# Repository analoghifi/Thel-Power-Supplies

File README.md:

# Thel-Power-Supplies
small symmetrical DC power supplies for audio (7W .. 110W | 2x5V .. 2x36V)  

--> https://web.archive.org/web/20180724064052/http://www.thel-audioworld.de/module/NT-HQ/NT-HQ.htm  

see as well the Thel "Black Pulsar" as a special\* kind of very high end power supply -> https://github.com/analoghifi/Thel-Black-Pulsar-PowerSupply  
\*(kinda "Class-A"-Power-Supply --> correctly: constant current parallel shunt voltage regulator)
  
----  
### Kicad projects in this repo:  
* [SPR5-HQ original](https://github.com/analoghifi/Thel-Power-Supplies/tree/main/SPR5-HQ/hardware/KiCad/original) | state: initial release v1.01 | like the original, 1-layer, THT
* [SPR5-HQ "original V2"](https://github.com/analoghifi/Thel-Power-Supplies/tree/main/SPR5-HQ/hardware/KiCad/original%20V2) | state: initial release v1.01 | like the original but improved PCB layout, 1-layer, THT
* [SPR5-HQ improved 2-layer](https://github.com/analoghifi/Thel-Power-Supplies/tree/main/SPR5-HQ/hardware/KiCad/improved%202-layer) | state: coming soon ... | improved, 2-layer PCB, THT

----

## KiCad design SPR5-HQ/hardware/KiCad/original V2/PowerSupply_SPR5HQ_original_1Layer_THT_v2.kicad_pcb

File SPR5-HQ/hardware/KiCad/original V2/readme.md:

this is not the original Thel PCB but it's very like\* the original with the following exceptions:  
* more massive ground and power supply PCB tracks  
* better component placement: D9 and D11 placed in a better location (this makes some small tracks obsolete)  
* better component placement: C8 and C11 rotated by 180° / C20 rotated by 90° / L1 and L2 rotated by 90°  
* therfore more space and more direct connections for ground and power PCB tracks
* almost all pads are 'thermal relief' pads now (for better solderability)
* more ventilation holes for the 2 heat sinks
  
\*(same schematic / same board dimensions / same 1-layer\*\* layout THT / same THT components in the same places on the board)  
\*\*(strictly speaking, this KiCad PCB is a two-layer PCB with plated-through holes, but you can also (let) produce it as a classic 1-layer PCB with non-plated holes if you wish, since all the tracks are on the bottom side only)  
  
----  
  
these are KiCad 6.x projects  
see how to get the proper 3D-Models from here: https://github.com/analoghifi/KiCad-3D-Models  

use kicanvas.org to see this KiCad-Project in your browser:  
https://kicanvas.org/?github=https%3A%2F%2Fgithub.com%2Fanaloghifi%2FThel-Power-Supplies%2Ftree%2Fmain%2FSPR5-HQ%2Fhardware%2FKiCad%2Foriginal%2520V2

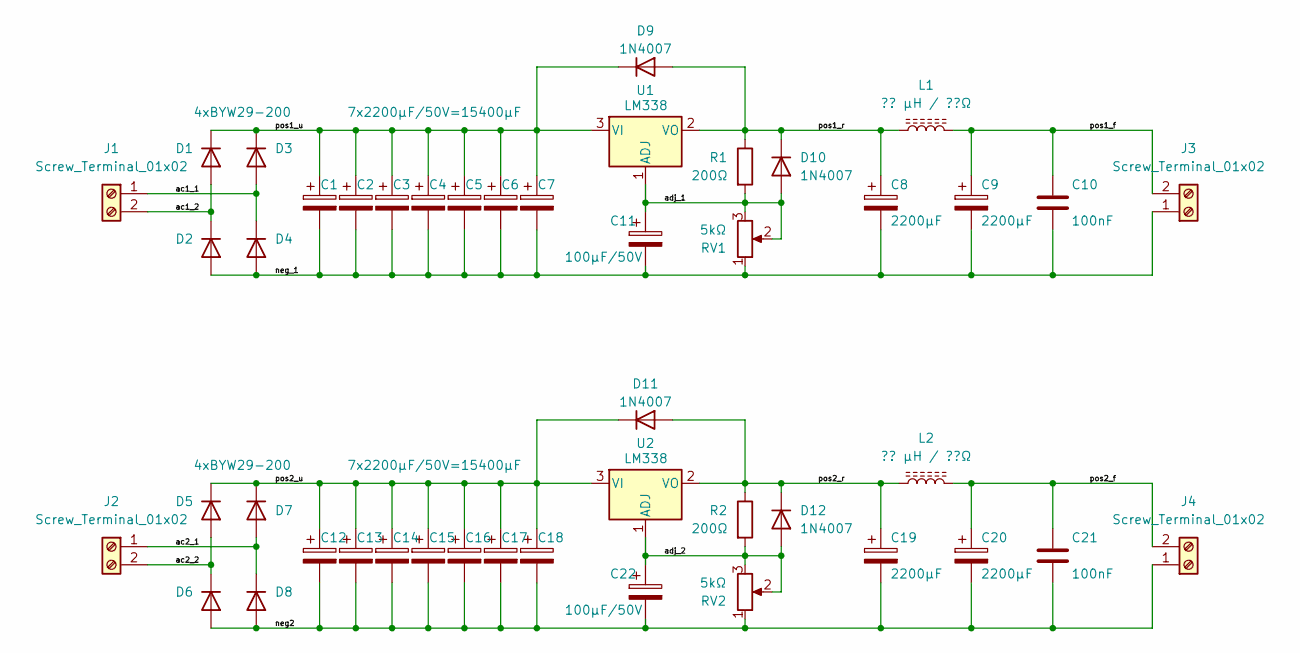
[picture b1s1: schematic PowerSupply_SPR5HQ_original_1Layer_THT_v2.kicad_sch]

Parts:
C1, C12: 7x2200µF/50V=15400µF; CP_Radial_Black_D16.2mm_H36mm_P7.50mm_minimal_silk
C2, C3, C4, C5, C6, C7, C8, C9, C13, C14, C15, C16, C17, C18, C19, C20: 2200µF; CP_Radial_Black_D16.2mm_H36mm_P7.50mm_minimal_silk
C10, C21: 100nF; C_Rect_L7.2mm_W2.5mm_P5.00mm_FKS2_FKP2_MKS2_MKP2
C11, C22: 100µF/50V; CP_Radial_Black_D8.2mm_H12.0mm_P3.50mm_minimal_silk
D1, D5: 4xBYW29-200; TO-220-2_Vertical_noSilk
D2, D3, D4, D6, D7, D8: BYW29-200; TO-220-2_Vertical_noSilk
D9, D11: 1N4007; D_DO-41_SOD81_very_short_P7.62mm_Horiz_V1_minSilk
D10, D12: 1N4007; D_DO-41_SOD81_short_P9.0mm_Horiz_minSilk
J1, J2, J3, J4: Screw_Terminal_01x02; TerminalBlock_Phoenix_PT-1,5-2-5.0-H_1x02_P5.00mm_Horizonta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
L1, L2: ?? µH / ??Ω; L_Radial_D8mm_H10mm_P5.08mm_no_silk
R1, R2: 200Ω; R_Axial_Short_L6.3mm_D2.5mm_P9.0mm_Horiz_minSilk
RV1, RV2: 5kΩ; Potentiometer_Bourns_3296W_Vertical
U1, U2: LM338; TO-220-3_Vertical

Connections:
/ac1_1: D3.2 (A), D4.1 (K), J1.1
/ac1_2: D1.2 (A), D2.1 (K), J1.2
/ac2_1: D7.2 (A), D8.1 (K), J2.1
/ac2_2: D5.2 (A), D6.1 (K), J2.2
/adj_1: C11.1, D10.2 (A), R1.2, RV1.2, RV1.3, U1.1 (ADJ)
/adj_2: C22.1, D12.2 (A), R2.2, RV2.2, RV2.3, U2.1 (ADJ)
/neg2: C12.2, C13.2, C14.2, C15.2, C16.2, C17.2, C18.2, C19.2, C20.2, C21.2, C22.2, D6.2 (A), D8.2 (A), J4.1, RV2.1
/neg_1: C1.2, C2.2, C3.2, C4.2, C5.2, C6.2, C7.2, C8.2, C9.2, C10.2, C11.2, D2.2 (A), D4.2 (A), J3.1, RV1.1
/pos1_f: C9.1, C10.1, J3.2, L1.2
/pos1_r: C8.1, D9.2 (A), D10.1 (K), L1.1, R1.1, U1.2 (VO)
/pos1_u: C1.1, C2.1, C3.1, C4.1, C5.1, C6.1, C7.1, D1.1 (K), D3.1 (K), D9.1 (K), U1.3 (VI)
/pos2_f: C20.1, C21.1, J4.2, L2.2
/pos2_r: C19.1, D11.2 (A), D12.1 (K), L2.1, R2.1, U2.2 (VO)
/pos2_u: C12.1, C13.1, C14.1, C15.1, C16.1, C17.1, C18.1, D5.1 (K), D7.1 (K), D11.1 (K), U2.3 (VI)

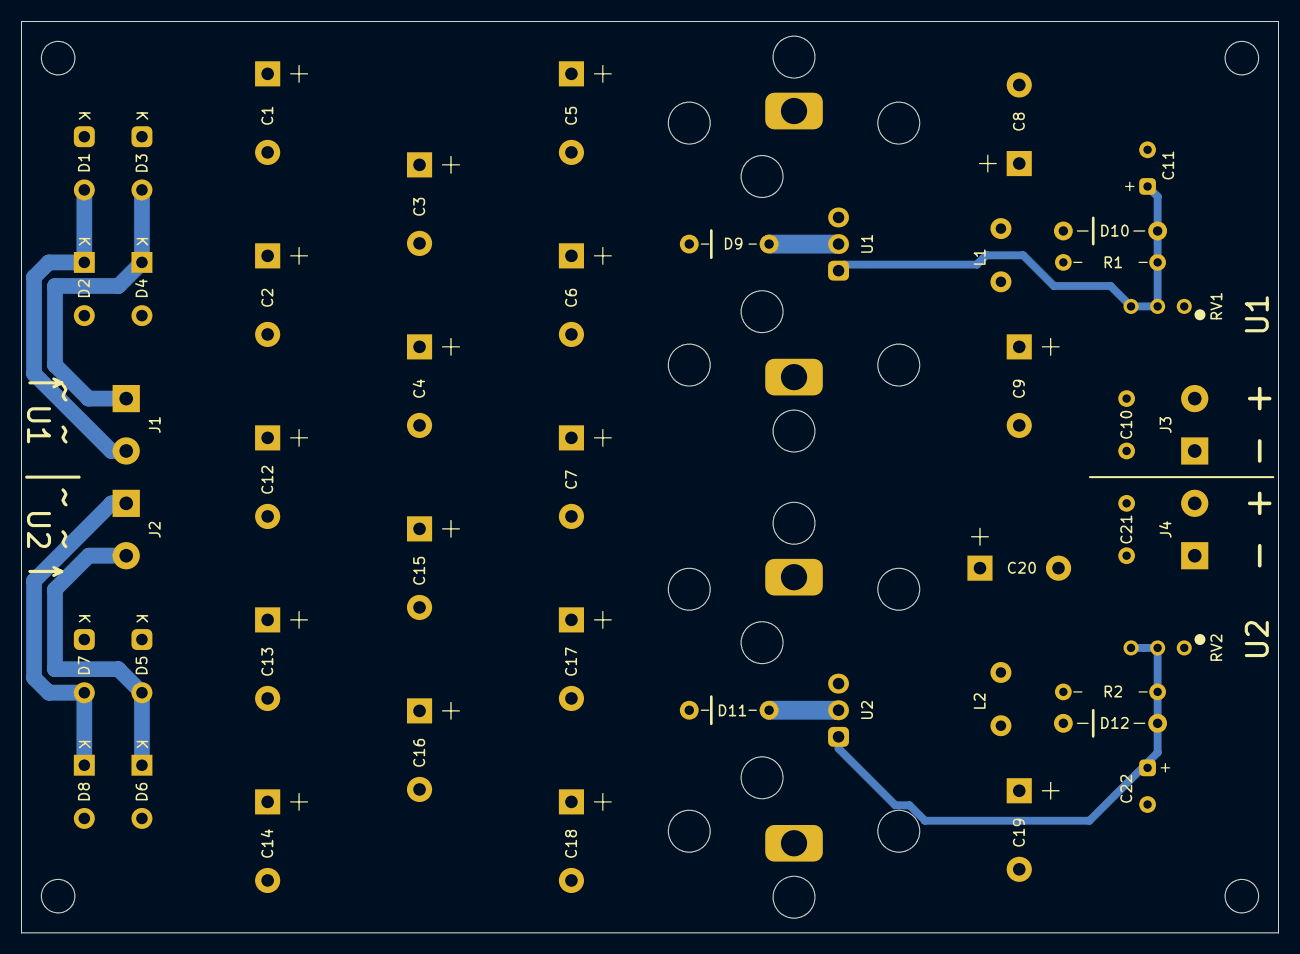
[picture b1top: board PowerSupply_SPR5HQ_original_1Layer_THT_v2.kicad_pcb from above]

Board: 2 copper layers, 120.0 x 87.0 mm, 46 parts (0 on the bottom side), 14 nets.
